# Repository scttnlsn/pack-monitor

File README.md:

# pack-monitor

Communicates with 1 or more [cell-monitor](https://github.com/scttnlsn/cell-monitor)s to monitor and
protect a battery pack.

## System Setup (Linux)

```
sudo apt update
sudo apt install cmake gcc-arm-none-eabi libnewlib-arm-none-eabi build-essential g++ libstdc++-arm-none-eabi-newlib
```

## SDK Setup

```
git clone https://github.com/raspberrypi/pico-sdk.git --branch master
cd pico-sdk
git submodule update --init
cd ..
export PICO_SDK_PATH=$(pwd)/pico-sdk
```

## Build

```
mkdir build
cd build
cmake ..
make -j4
```

## References

Pico:

* https://datasheets.raspberrypi.org/pico/Pico-R3-A4-Pinout.pdf
* https://datasheets.raspberrypi.org/rp2040/rp2040-datasheet.pdf
* https://datasheets.raspberrypi.org/pico/raspberry-pi-pico-c-sdk.pdf
* https://raspberrypi.github.io/pico-sdk-doxygen/

Modbus:

* https://www.fernhillsoftware.com/help/drivers/modbus/modbus-protocol.html
* https://minimalmodbus.readthedocs.io/en/stable/modbusdetails.html

Onewire:

* https://www.maximintegrated.com/en/design/technical-documents/app-notes/1/126.html

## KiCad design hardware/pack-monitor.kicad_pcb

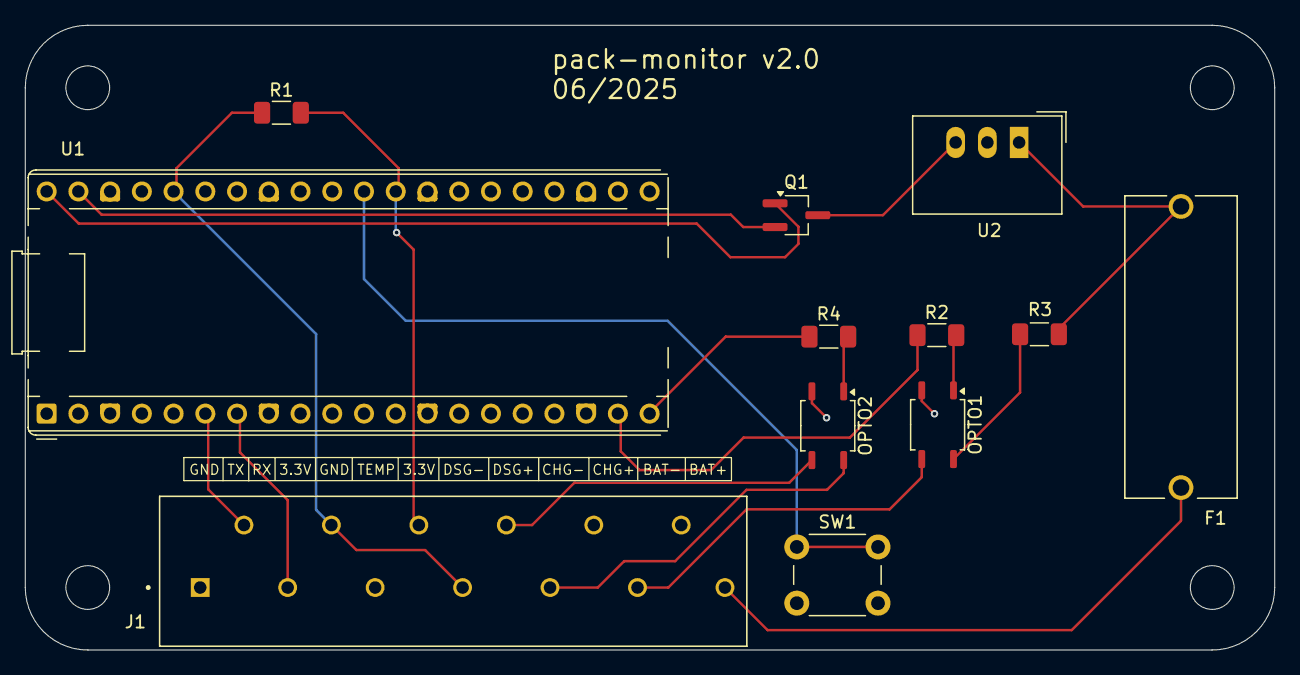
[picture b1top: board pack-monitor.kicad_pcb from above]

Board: 2 copper layers, 100.0 x 50.0 mm, 12 parts (0 on the bottom side), 19 nets.

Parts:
F1: 4628; FUSE_4628
J1: 1985302; PHOENIX_1985302
OPTO1, OPTO2: SSR; SOP-4_3.8x4.1mm_P2.54mm
Q1: PMOS; TSOT-23_HandSoldering
R1: 4.7k; R_1206_3216Metric_Pad1.30x1.75mm_HandSolder
R2, R3, R4: 1k; R_1206_3216Metric_Pad1.30x1.75mm_HandSolder
SW1: RESET_BTN; SW_PUSH_6mm
U1: Pico; RaspberryPi_Pico_Common_THT
U2: TSR 0.5-2450; Converter_DCDC_TRACO_TSR-1_THT

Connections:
+3.3V: J1.4, J1.7, R1.1, U1.36 (3V3)
+BATT: F1.1, J1.13
/BATT_V: F1.2, R3.1, U2.1 (IN)
/CELLS_RX: J1.3, U1.7 (GPIO5)
/CELLS_TX: J1.2, U1.6 (GPIO4)
/CHG: R2.1, U1.19 (GPIO14)
/CHG+: J1.11, OPTO1.3
/DSG: R4.1, U1.20 (GPIO15)
/DSG+: J1.9, OPTO2.4
/DSG-: J1.8, OPTO2.3
/RESET: SW1.1, U1.30 (RUN)
/TEMP: J1.6, R1.2, U1.29 (GPIO22)
/VBUS: Q1.1 (G), U1.40 (VBUS)
/VSYS: Q1.2 (S), U1.39 (VSYS)
GND: J1.1, J1.5, J1.10, J1.12, OPTO1.2, OPTO2.2, SW1.2, U1.3 (GND), U1.8 (GND), U1.13 (GND), U1.18 (GND), U1.23 (GND), U1.28 (GND), U1.33 (AGND), U1.38 (GND), U2.2 (GND)
unnamed: OPTO1.1, R2.2
unnamed: OPTO1.4, R3.2
unnamed: OPTO2.1, R4.2
unnamed: Q1.3 (D), U2.3 (OUT)

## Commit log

2018-05-22 Cell voltage monitoring, protection checks
2018-05-22 Ensure the expected number of cell monitors are connected
2018-05-22 Added quick README
2018-05-30 Added current measurements and calibration
2018-06-20 Default to 8 cells
2018-06-20 Fix discharge enable
2018-07-06 Fix status value
2018-07-06 Short delay before zeroing current
2018-07-16 Added SOC tracking
2018-07-16 Added 1 second watchdog
2018-07-16 Move pack voltage divider to config file
2018-07-16 Update serial output format
2018-08-09 Fix pack voltage divider
2018-08-09 Update .python-version
2018-08-11 Move max voltage error to config file
2018-08-27 Added charge and discharge coulomb counting
2018-10-04 Added modbus interface for reading data via serial
2018-10-05 Added modbus client script
2018-10-05 Flush stdout after outputting each line
2018-10-10 Added error timeout before fault is triggered
2018-10-10 Cast client interval arg to int
2018-10-10 Lower modbus baud rate
2021-02-05 Initial pico setup
2021-02-09 Added modbus RTU
2021-02-09 Added onewire and ds18b20 drivers
2021-02-11 Added cell monitors interface
2024-09-20 Update setup
2024-09-20 Gracefully handle cell monitor disconnection/error
2024-09-20 Improved packet handling
2024-09-20 Add events abstraction
2024-09-27 Cell monitor calibration through modbus interface
2024-09-28 Support arbitrary sized elements in ringbuf
2024-09-28 Add round trip time register
2025-04-14 Send packets to cell monitors serially
2025-04-14 Added chg/dsg protection
2025-04-14 Expose status, protection and error in registers
2025-05-09 Fix decoding write bit
2025-05-16 Bounds check on register index
2025-05-16 More error handling, remove voltage_ref registers
2025-05-16 Update cmake config
2025-05-16 Update client script, add calibration script
2025-05-23 Add KiCad files
2025-05-30 Update pmos pins
